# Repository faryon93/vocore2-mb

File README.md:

# VoCore2 Motherboard

* 1x Ethernet Breakout
* 3x Mini-PCIe Slot (USB Connection via USB 2.0 Hub)
* MicroSD Card
* FTDI console UART
* Passive PoE or Phoenix-style connector for power
* Buzzer
* SPI Flash Breakout Header

## Board

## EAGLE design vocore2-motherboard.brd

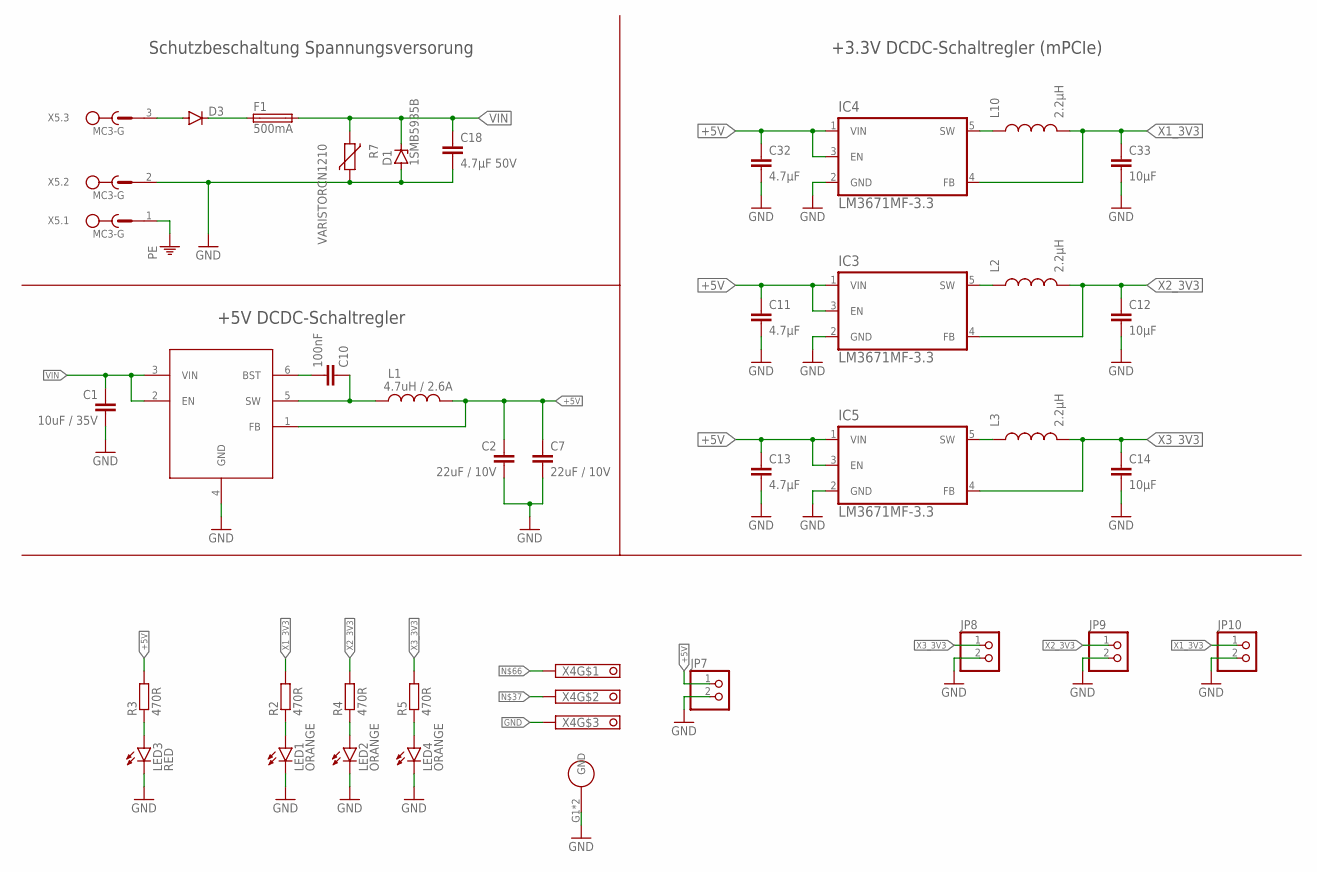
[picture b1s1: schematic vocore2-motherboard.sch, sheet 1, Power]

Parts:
C1: 10uF / 35V; C0805; DIGIKEY 490-13248-1-ND
C2, C7: 22uF / 10V; C0805; DIGIKEY 490-10511-1-ND
C10: 100nF; C0805
C11, C13, C32: 4.7µF; C0603; DIGIKEY 1276-2087-1-ND
C12, C14, C33: 10µF; C0603
C18: 4.7µF 50V; C1206; DIGIKEY 587-2994-1-ND
D1: 1SMB5935B; SMB; FARNELL 1431177
D3: DIODE-SMB; SMB; FARNELL 1858651
F1: 500mA; 1812; LCSC C17313
IC1: AP63205; SOT23-6
IC3, IC4, IC5: LM3671MF-3.3; SOT95P284X122-5N; DIGIKEY LM3671MF-3.3/NOPBCT-ND
JP7: PINHD-1X2_2.54; 1X02
JP8, JP9, JP10: PINHD-1X2; 1X02
L1: 4.7uH / 2.6A; 4.90X4.90; DIGIKEY 587-3605-2-ND
L2, L3, L10: 2.2µH; SO3314; DIGIKEY 445-8725-1-ND
LED1, LED2, LED4: ORANGE; CHIP-LED0805; DIGIKEY 160-1445-1-ND
LED3: RED; CHIP-LED0805; DIGIKEY 160-1447-1-ND
R2, R3, R4, R5: 470R; R0603
R7: VARISTORCN1210; CT/CN1210; FARNELL 1636457
X4: BM03B-SRSS-TB
X5: MC3-G; DIGIKEY ‎277-1207-ND‎;‎277-13872-ND‎

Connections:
+5V: C2.1, C7.1, C11.1, C13.1, C32.1, IC1.1 (FB), IC3.1 (VIN), IC3.3 (EN), IC4.1 (VIN), IC4.3 (EN), IC5.1 (VIN), IC5.3 (EN), JP7.1, L1.P$2 (2), R3.2; also elsewhere on the board
+24V: D3.C, F1.1; also elsewhere on the board
GND: C1.2, C2.2, C7.2, C11.2, C12.2, C13.2, C14.2, C18.2, C32.2, C33.2, D1.A, IC1.4 (GND), IC3.2 (GND), IC4.2 (GND), IC5.2 (GND), JP7.2, JP8.2, JP9.2, JP10.2, LED1.C, LED2.C, LED3.C, LED4.C, R7.1, X4.3 (K), X4.G1 (GND), X4.G2 (GND), X5.2; also elsewhere on the board
unnamed: C10.1, IC1.5 (SW), L1.P$1 (1)
unnamed: IC3.5 (SW), L2.1
unnamed: IC5.5 (SW), L3.1
unnamed: LED3.A, R3.1
unnamed: LED1.A, R2.1
unnamed: LED2.A, R4.1
unnamed: LED4.A, R5.1
unnamed 43: X4.2 (K); also elsewhere on the board
unnamed: IC4.5 (SW), L10.1
unnamed: D3.A, X5.3
unnamed: C10.2, IC1.6 (BST)
unnamed 65: X4.1 (K); also elsewhere on the board
PE: X5.1
VIN: C1.1, C18.1, D1.C, F1.2, IC1.2 (EN), IC1.3 (VIN), R7.2
X1_3V3: C33.1, IC4.4 (FB), JP10.1, L10.2, R2.2; also elsewhere on the board
X2_3V3: C12.1, IC3.4 (FB), JP9.1, L2.2, R4.2; also elsewhere on the board
X3_3V3: C14.1, IC5.4 (FB), JP8.1, L3.2, R5.2; also elsewhere on the board

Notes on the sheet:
Schutzbeschaltung Spannungsversorung
+5V DCDC-Schaltregler
+3.3V DCDC-Schaltregler (mPCIe)

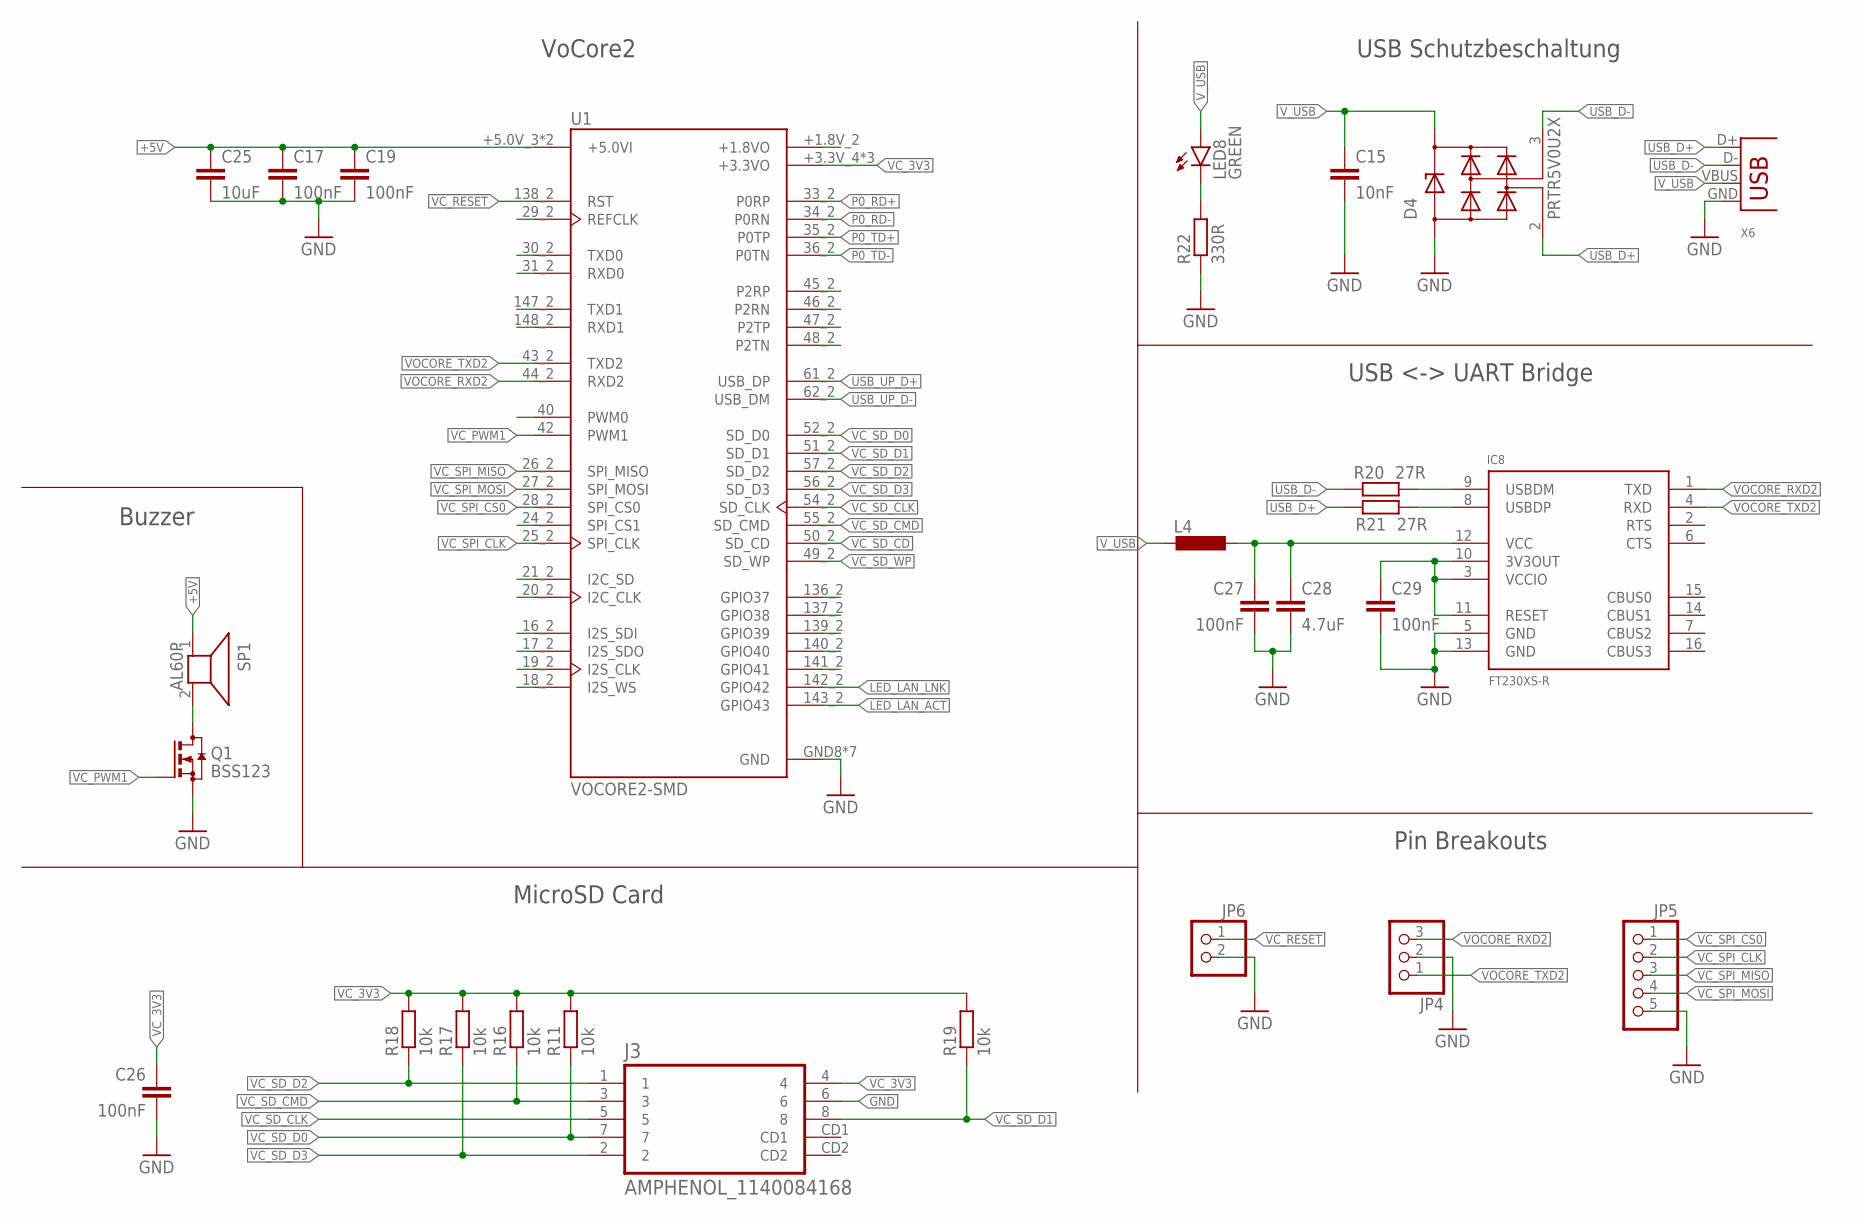
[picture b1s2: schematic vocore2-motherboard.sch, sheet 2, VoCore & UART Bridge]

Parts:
C15: 10nF; C0603
C17, C19, C26, C27, C29: 100nF; C0603
C25: 10uF; C0603
C28: 4.7uF; C0603
D4: PRTR5V0U2X; SOT143; DIGIKEY 1727-3884-1-ND
IC8: FT230XS-R; SSOP16-0.635-5X4MM
J3: AMPHENOL_1140084168
JP4: PINHD-1X3; 1X03
JP5: PINHD-1X5; 1X05
JP6: PINHD-1X2_2.54; 1X02
L4: L-EUL0805; L0805; DIGIKEY 490-1054-1-ND
LED8: GREEN; CHIP-LED0805; DIGIKEY 160-1446-1-ND
Q1: BSS123; SOT23; DIGIKEY BSS123LT1GOSCT-ND‎
R11, R16, R17, R18, R19: 10k; R0603
R20, R21: 27R; R0603
R22: 330R; R0603
SP1: AL60P; LCSC C252917
U1: VOCORE2-SMD; VOCORE2_SMD
X6: USB-MB-S

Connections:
!VC_RESET: JP6.1, U1.138_2 (RST)
+5V: C17.1, C19.1, C25.1, SP1.1, U1.+5.0V_3 (+5.0VI), U1.+5.0V_4 (+5.0VI); also elsewhere on the board
FT230_VCCIO: C29.1, IC8.3 (VCCIO), IC8.10 (3V3OUT), IC8.11 (RESET)
GND: C15.2, C17.2, C19.2, C25.2, C26.2, C27.2, C28.2, C29.2, D4.1 (GND), IC8.5 (GND), IC8.13 (GND), J3.6, JP4.2, JP5.5, JP6.2, Q1.2 (S), R22.1, U1.GND8 (GND), U1.GND9 (GND), U1.GND10 (GND), U1.GND11 (GND), U1.GND12 (GND), U1.GND13 (GND), U1.GND14 (GND), X6.GND; also elsewhere on the board
LED_LAN_ACT: U1.143_2 (GPIO43); also elsewhere on the board
LED_LAN_LNK: U1.142_2 (GPIO42); also elsewhere on the board
unnamed: Q1.3 (D), SP1.2
unnamed: C27.1, C28.1, IC8.12 (VCC), L4.1
unnamed: IC8.9 (USBDM), R20.2
unnamed: IC8.8 (USBDP), R21.1
unnamed: LED8.C, R22.2
P0_RD+: U1.33_2 (P0RP); also elsewhere on the board
P0_RD-: U1.34_2 (P0RN); also elsewhere on the board
P0_TD+: U1.35_2 (P0TP); also elsewhere on the board
P0_TD-: U1.36_2 (P0TN); also elsewhere on the board
USB_D+: D4.2 (IO1), R21.2, X6.D+
USB_D-: D4.3 (IO2), R20.1, X6.D-
USB_UP_D+: U1.61_2 (USB_DP); also elsewhere on the board
USB_UP_D-: U1.62_2 (USB_DM); also elsewhere on the board
VC_3V3: C26.1, J3.4, R11.2, R16.2, R17.2, R18.2, R19.2, U1.+3.3V_4 (+3.3VO), U1.+3.3V_5 (+3.3VO), U1.+3.3V_6 (+3.3VO); also elsewhere on the board
VC_PWM1: Q1.1 (G), U1.42 (PWM1)
VC_SD_CD: U1.50_2 (SD_CD)
VC_SD_CLK: J3.5, U1.54_2 (SD_CLK)
VC_SD_CMD: J3.3, R16.1, U1.55_2 (SD_CMD)
VC_SD_D0: J3.7, R11.1, U1.52_2 (SD_D0)
VC_SD_D1: J3.8, R19.1, U1.51_2 (SD_D1)
VC_SD_D2: J3.1, R18.1, U1.57_2 (SD_D2)
VC_SD_D3: J3.2, R17.1, U1.56_2 (SD_D3)
VC_SD_WP: U1.49_2 (SD_WP)
VC_SPI_CLK: JP5.2, U1.25_2 (SPI_CLK)
VC_SPI_CS0: JP5.1, U1.28_2 (SPI_CS0)
VC_SPI_MISO: JP5.3, U1.26_2 (SPI_MISO)
VC_SPI_MOSI: JP5.4, U1.27_2 (SPI_MOSI)
VOCORE_RXD2: IC8.1 (TXD), JP4.3, U1.44_2 (RXD2)
VOCORE_TXD2: IC8.4 (RXD), JP4.1, U1.43_2 (TXD2)
V_USB: C15.1, D4.4 (VCC), L4.2, LED8.A, X6.VBUS

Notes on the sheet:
USB Schutzbeschaltung
Pin Breakouts
USB <-> UART Bridge
VoCore2
MicroSD Card
Buzzer

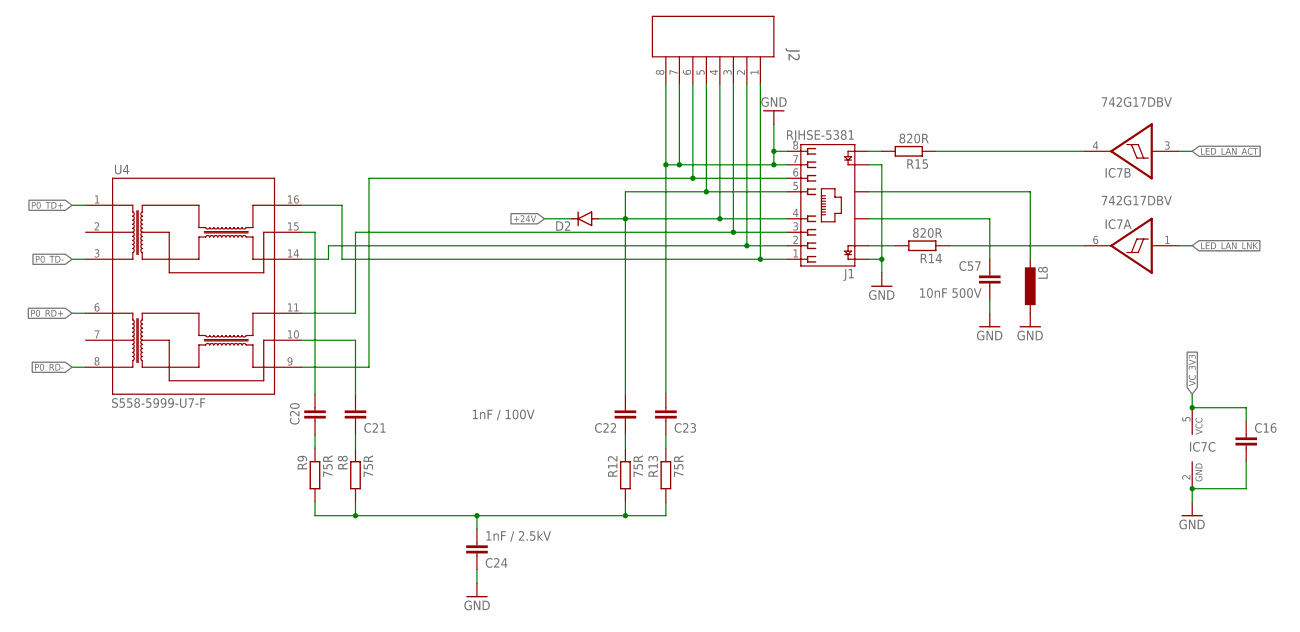
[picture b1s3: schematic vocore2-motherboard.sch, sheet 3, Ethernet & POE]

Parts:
C16: 100nF; C0603; DIGIKEY 490-4780-1-ND
C20, C21, C22, C23: 1nF / 100V; C0603; DIGIKEY 490-4780-1-ND
C24: 1nF / 2.5kV; C1808; DIGIKEY 399-7246-1-ND
C57: 10nF 500V; C0805; DIGIKEY 709-1021-1-ND
D2: DIODE-SMB; SMB; FARNELL 1858651
IC7: 742G17DBV; DBV_R-PDSO-G6; DIGIKEY 296-13010-1-ND
J1: RJHSE-5381; AMPHENOL_RJHSE-5381
J2: TE_1775470-8; CONN8_1775470-8; DIGIKEY A100058CT-ND
L8: L-EUL0805; L0805; DIGIKEY 490-1054-1-ND
R8, R9, R12, R13: 75R; R0603; DIGIKEY RNCP0603FTD75R0CT-ND‎
R14, R15: 820R; R0603; DIGIKEY A129687CT-ND
U4: S558-5999-U7-F

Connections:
+24V: D2.C; also elsewhere on the board
GND: C16.2, C23.2, C24.1, C57.2, IC7.2 (GND), J1.7, J1.8, J1.9, J1.11, J2.7, J2.8, L8.1; also elsewhere on the board
LED_LAN_ACT: IC7.3 (I); also elsewhere on the board
LED_LAN_LNK: IC7.1 (I); also elsewhere on the board
unnamed: C20.2, U4.15 (TX_CT)
unnamed: C21.2, U4.10 (RX_CT)
unnamed: C21.1, R8.1
unnamed: C20.1, R9.1
unnamed: C22.1, R12.1
unnamed: C23.1, R13.1
unnamed: C24.2, R8.2, R9.2, R12.2, R13.2
unnamed 43: IC7.4 (O), R15.1; also elsewhere on the board
unnamed: J1.12, R15.2
unnamed: J1.10, R14.2
unnamed: J1.S2, L8.2
unnamed: C57.1, J1.S1
unnamed 65: IC7.6 (O), R14.1; also elsewhere on the board
P0_RD+: U4.6 (RD+); also elsewhere on the board
P0_RD-: U4.8 (RD-); also elsewhere on the board
P0_TD+: U4.1 (TD+); also elsewhere on the board
P0_TD-: U4.3 (TD-); also elsewhere on the board
POE_V+: C22.2, D2.A, J1.4, J1.5, J2.4, J2.5
RX+: J1.3, J2.3, U4.11 (RX+)
RX-: J1.6, J2.6, U4.9 (RX-)
TX+: J1.1, J2.1, U4.16 (TX+)
TX-: J1.2, J2.2, U4.14 (TX-)
VC_3V3: C16.1, IC7.5 (VCC); also elsewhere on the board

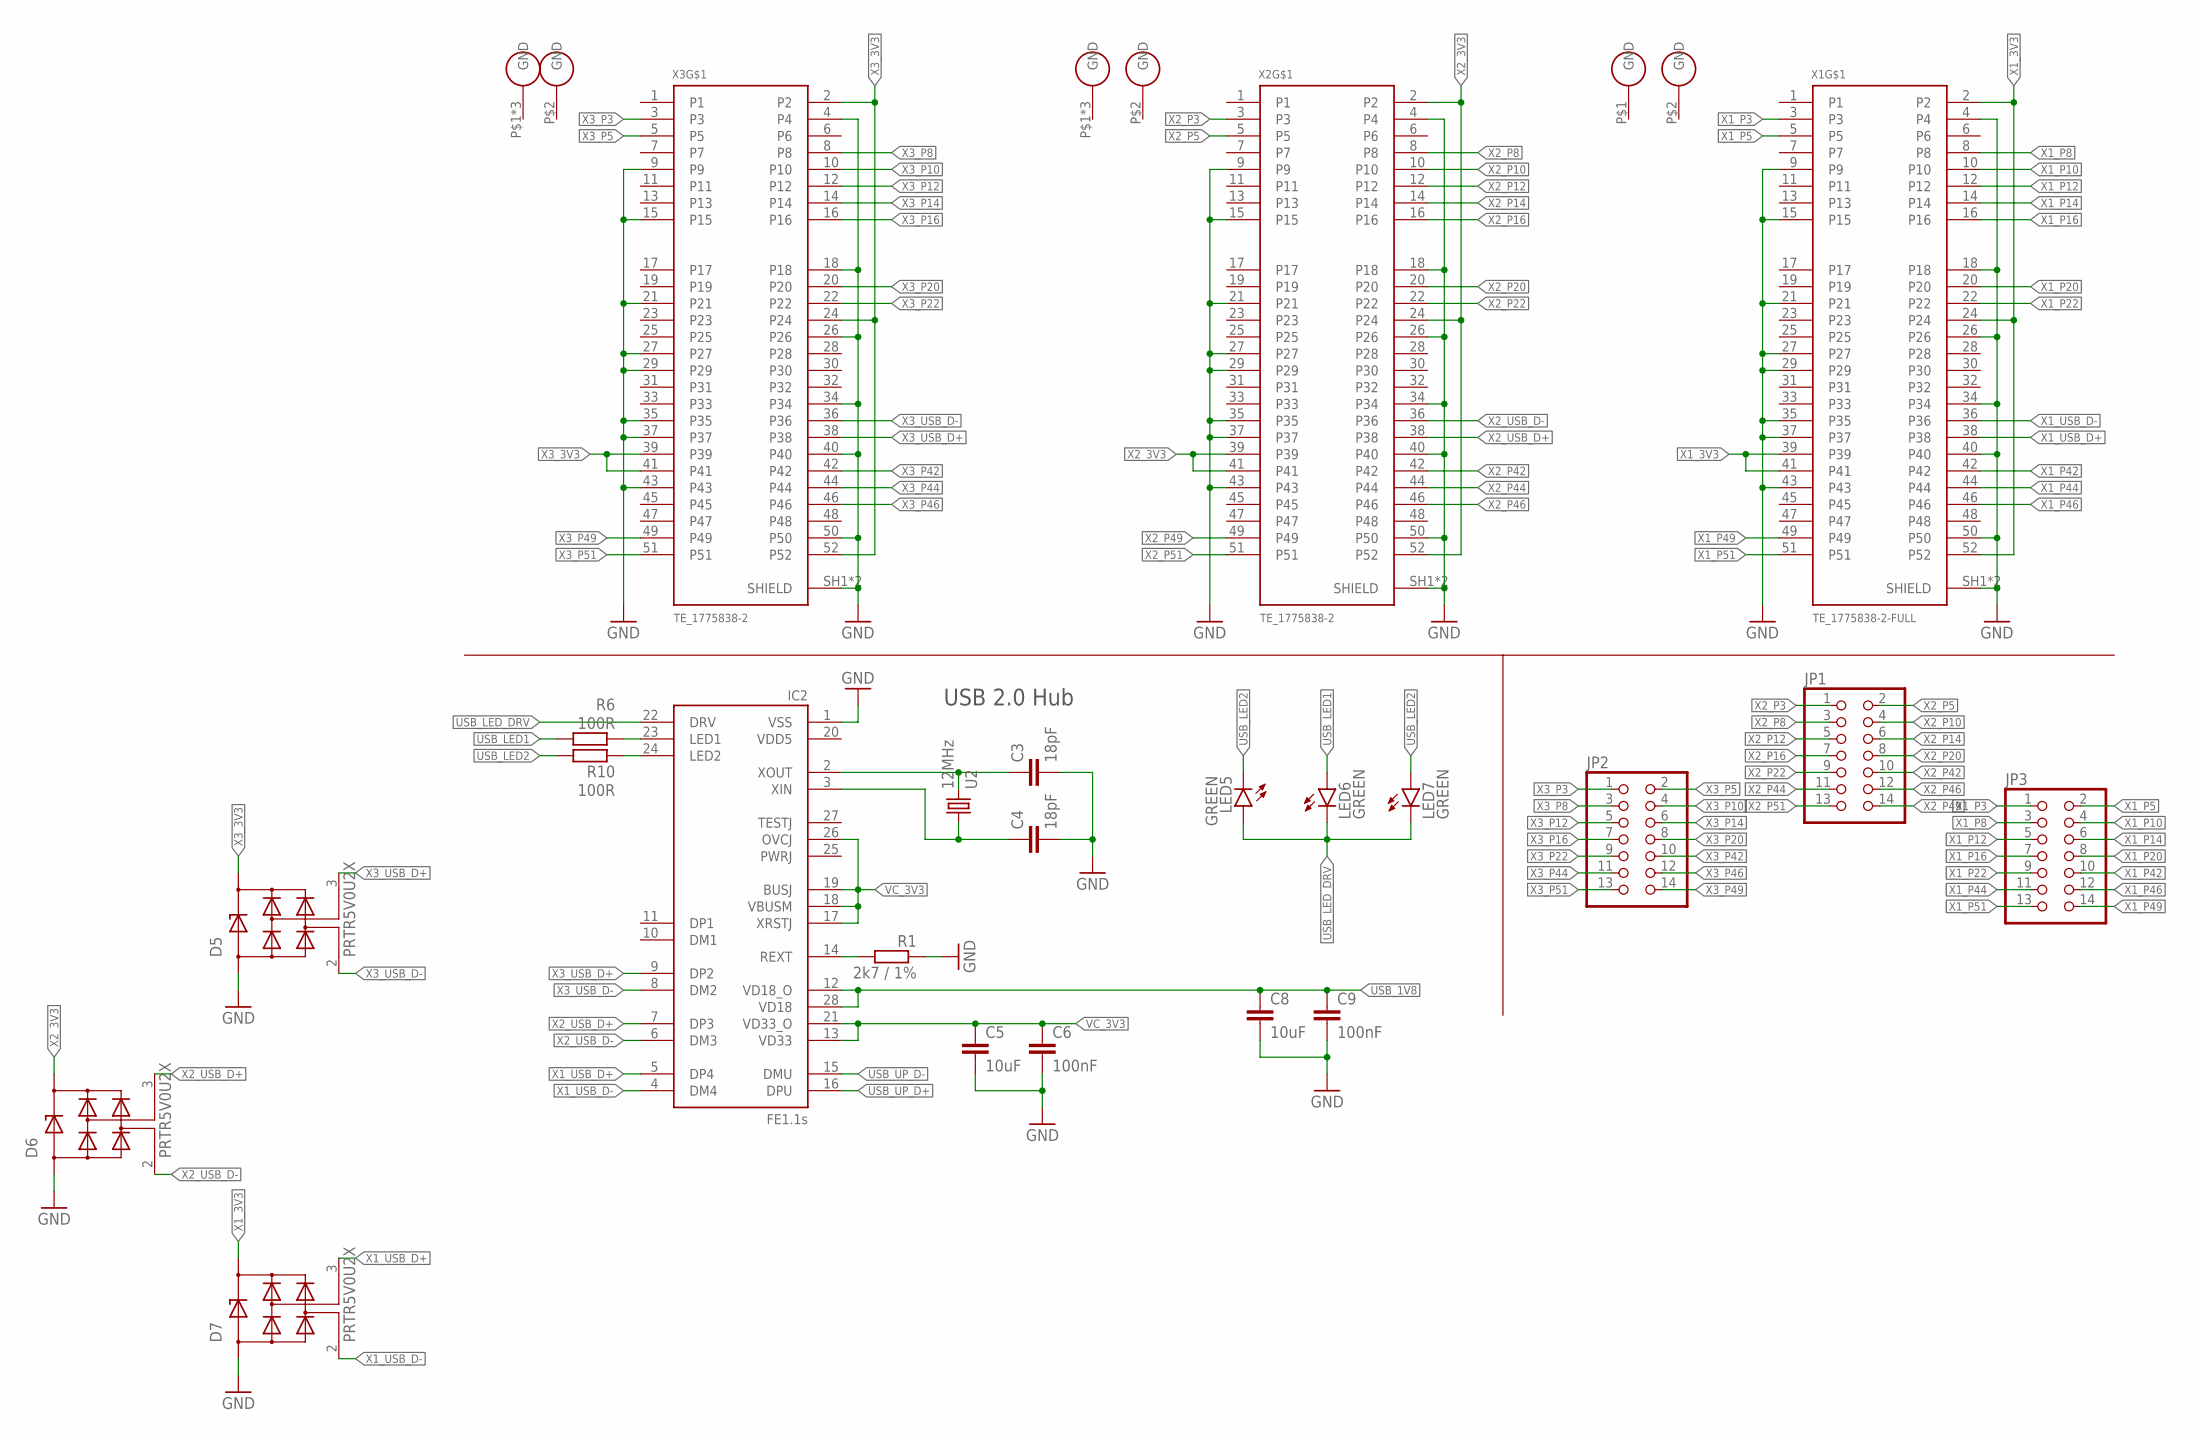
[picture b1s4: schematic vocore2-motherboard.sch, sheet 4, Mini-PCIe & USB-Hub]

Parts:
C3, C4: 18pF; C0603
C5, C8: 10uF; C0603
C6, C9: 100nF; C0603
D5, D6, D7: PRTR5V0U2X; SOT143; DIGIKEY 1727-3884-1-ND
IC2: FE1.1S; FE1.1S_SSOP-28
JP1, JP2, JP3: PINHD-2X7; 2X07
LED5, LED6, LED7: GREEN; CHIP-LED0805; DIGIKEY 160-1446-1-ND
R1: 2k7 / 1%; R0603; DIGIKEY RR08P2.7KDCT-ND
R6, R10: 100R; R0603
U2: 12MHz; 7A; FARNELL 1841940
X1: TE_1775838-2-FULL
X2, X3: TE_1775838-2

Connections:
GND: C3.2, C4.2, C5.2, C6.2, C8.2, C9.2, D5.1 (GND), D6.1 (GND), D7.1 (GND), IC2.1 (VSS), R1.1, X1.4, X1.9, X1.15, X1.18, X1.21, X1.26, X1.27, X1.29, X1.34, X1.35, X1.37, X1.40, X1.43, X1.50, X1.P$1 (GND), X1.P$2 (GND), X1.SH1 (SHIELD), X1.SH2 (SHIELD), X2.4, X2.9, X2.15, X2.18, X2.21, X2.26, X2.27, X2.29, X2.34, X2.35, X2.37, X2.40, X2.43, X2.50, X2.P$1 (GND), X2.P$2 (GND), X2.P$3 (GND), X2.P$4 (GND), X2.SH1 (SHIELD), X2.SH2 (SHIELD), X3.4, X3.9, X3.15, X3.18, X3.21, X3.26, X3.27, X3.29, X3.34, X3.35, X3.37, X3.40, X3.43, X3.50, X3.P$1 (GND), X3.P$2 (GND), X3.P$3 (GND), X3.P$4 (GND), X3.SH1 (SHIELD), X3.SH2 (SHIELD); also elsewhere on the board
unnamed: C3.1, IC2.2 (XOUT), U2.2
unnamed: C4.1, IC2.3 (XIN), U2.1
unnamed: IC2.14 (REXT), R1.2
unnamed: IC2.23 (LED1), R6.1
unnamed: IC2.24 (LED2), R10.1
USB_1V8: C8.1, C9.1, IC2.12 (VD18_O), IC2.28 (VD18)
USB_LED1: LED6.A, R6.2
USB_LED2: LED5.C, LED7.A, R10.2
USB_LED_DRV: IC2.22 (DRV), LED5.A, LED6.C, LED7.C
USB_UP_D+: IC2.16 (DPU); also elsewhere on the board
USB_UP_D-: IC2.15 (DMU); also elsewhere on the board
VC_3V3: C5.1, C6.1, IC2.13 (VD33), IC2.17 (XRSTJ), IC2.18 (VBUSM), IC2.19 (BUSJ), IC2.21 (VD33_O), IC2.26 (OVCJ); also elsewhere on the board
X1_3V3: D7.4 (VCC), X1.2, X1.24, X1.39, X1.41, X1.52; also elsewhere on the board
X1_P3: JP3.1, X1.3
X1_P5: JP3.2, X1.5
X1_P8: JP3.3, X1.8
X1_P10: JP3.4, X1.10
X1_P12: JP3.5, X1.12
X1_P14: JP3.6, X1.14
X1_P16: JP3.7, X1.16
X1_P20: JP3.8, X1.20
X1_P22: JP3.9, X1.22
X1_P42: JP3.10, X1.42
X1_P44: JP3.11, X1.44
X1_P46: JP3.12, X1.46
X1_P49: JP3.14, X1.49
X1_P51: JP3.13, X1.51
X1_USB_D+: D7.3 (IO2), IC2.5 (DP4), X1.38
X1_USB_D-: D7.2 (IO1), IC2.4 (DM4), X1.36
X2_3V3: D6.4 (VCC), X2.2, X2.24, X2.39, X2.41, X2.52; also elsewhere on the board
X2_P3: JP1.1, X2.3
X2_P5: JP1.2, X2.5
X2_P8: JP1.3, X2.8
X2_P10: JP1.4, X2.10
X2_P12: JP1.5, X2.12
X2_P14: JP1.6, X2.14
X2_P16: JP1.7, X2.16
X2_P20: JP1.8, X2.20
X2_P22: JP1.9, X2.22
X2_P42: JP1.10, X2.42
X2_P44: JP1.11, X2.44
X2_P46: JP1.12, X2.46
X2_P49: JP1.14, X2.49
X2_P51: JP1.13, X2.51
X2_USB_D+: D6.3 (IO2), IC2.7 (DP3), X2.38
X2_USB_D-: D6.2 (IO1), IC2.6 (DM3), X2.36
X3_3V3: D5.4 (VCC), X3.2, X3.24, X3.39, X3.41, X3.52; also elsewhere on the board
X3_P3: JP2.1, X3.3
X3_P5: JP2.2, X3.5
X3_P8: JP2.3, X3.8
X3_P10: JP2.4, X3.10
X3_P12: JP2.5, X3.12
X3_P14: JP2.6, X3.14
X3_P16: JP2.7, X3.16
X3_P20: JP2.8, X3.20
X3_P22: JP2.9, X3.22
X3_P42: JP2.10, X3.42
X3_P44: JP2.11, X3.44
X3_P46: JP2.12, X3.46
X3_P49: JP2.14, X3.49
X3_P51: JP2.13, X3.51
X3_USB_D+: D5.3 (IO2), IC2.9 (DP2), X3.38
X3_USB_D-: D5.2 (IO1), IC2.8 (DM2), X3.36

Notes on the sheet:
USB 2.0 Hub

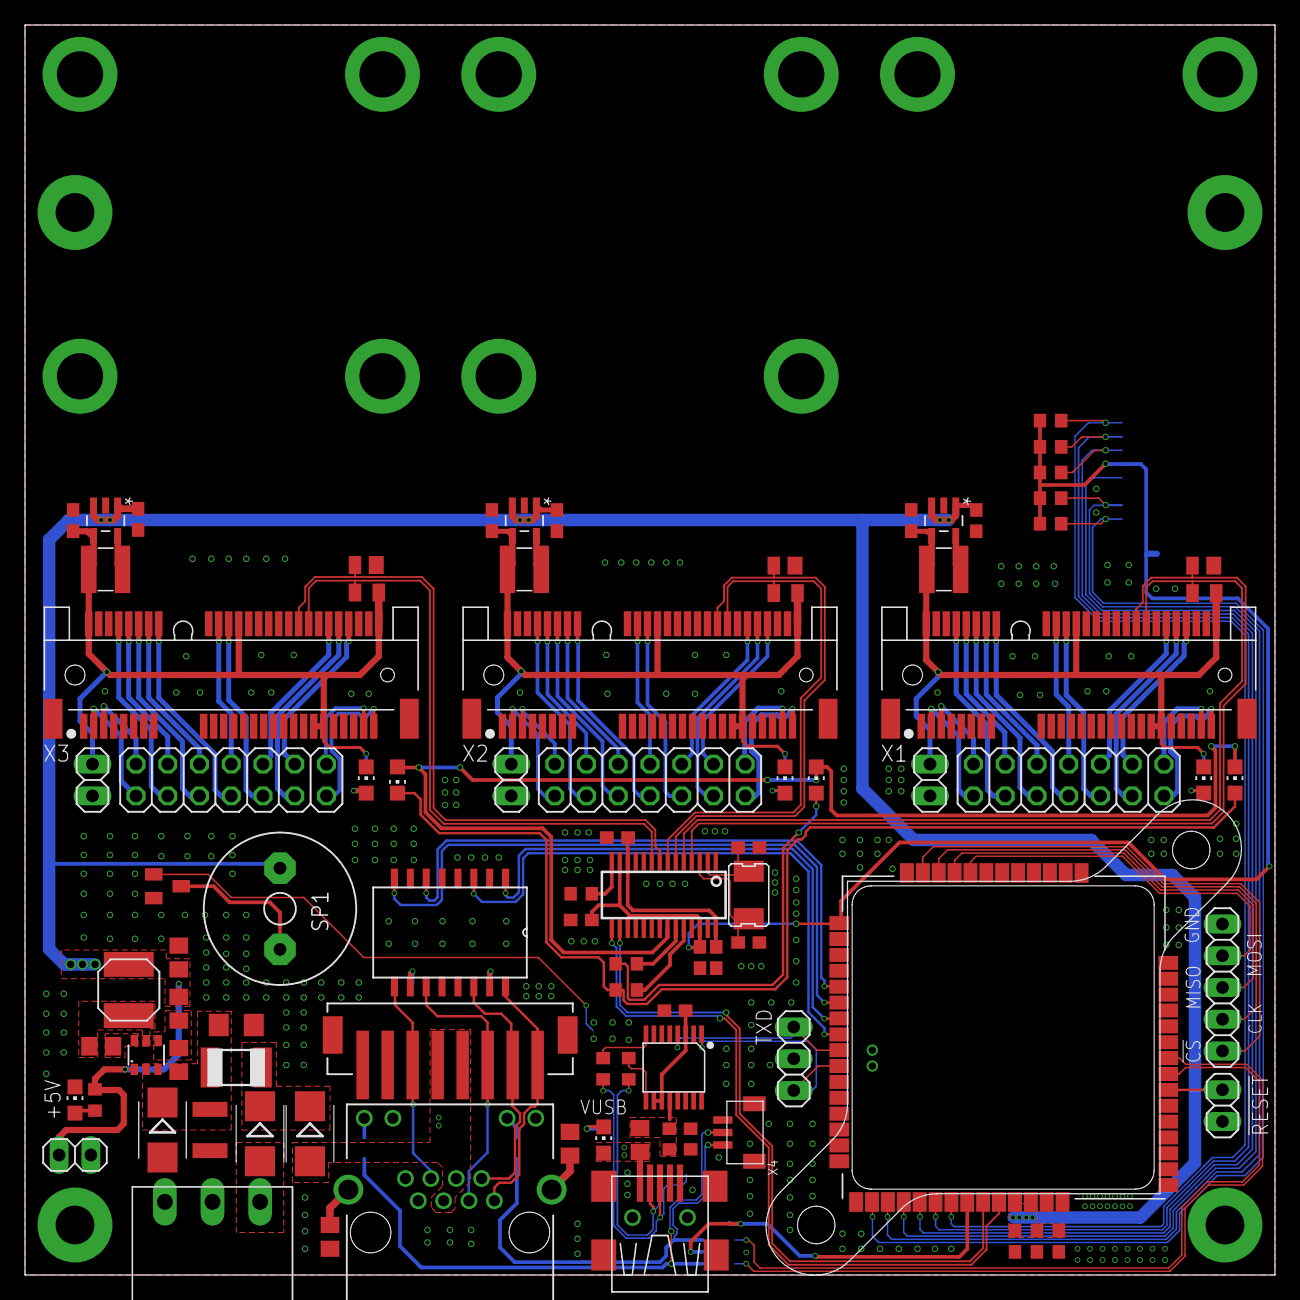
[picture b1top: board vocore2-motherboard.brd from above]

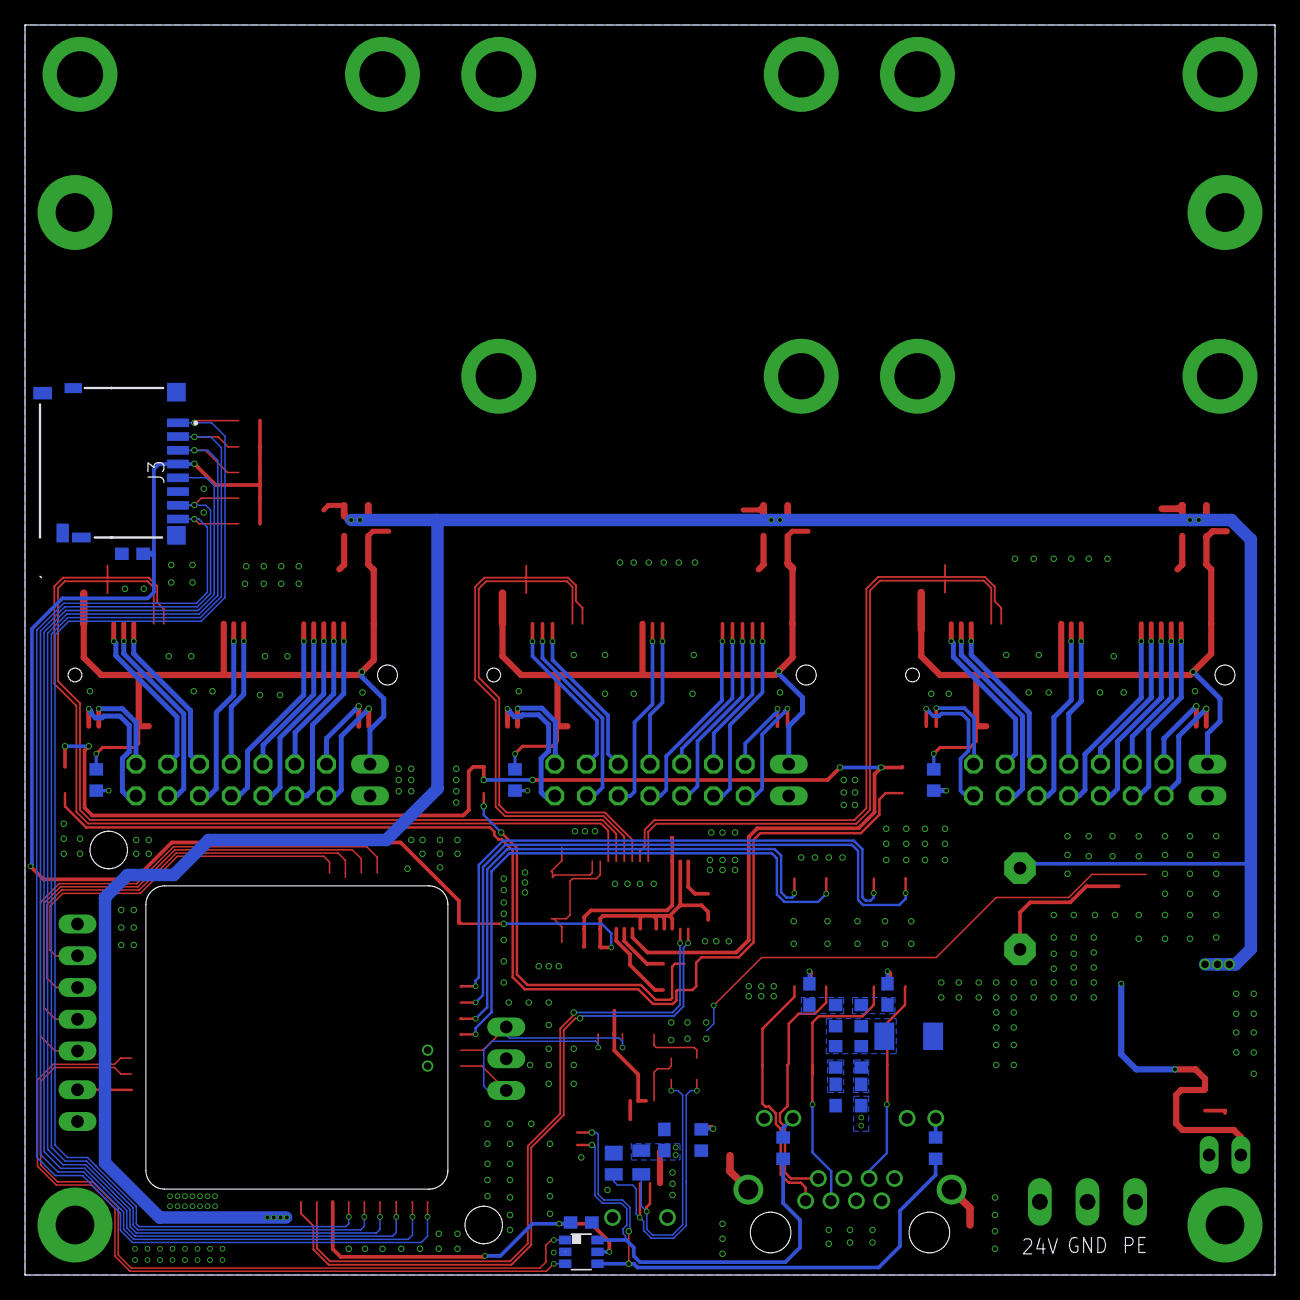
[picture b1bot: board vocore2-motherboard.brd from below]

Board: 2 copper layers, 100.0 x 100.0 mm, 108 parts (21 on the bottom side), 124 nets.

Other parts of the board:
U$1: ATS-P1-138-C2-R0

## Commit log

2019-11-04 fix: moved LAN_LED_ACT to gpio43
    gpio43 can be configured to represent the LNK/ACT state of the Ethernt
    PHYs Port 0.
2019-11-04 fix: typo in partname LM3761MF -> LM3671MF
2019-11-04 feat: added digikey part numbers
2019-11-04 fix: proper colors for leds
    PWR = red
    MPCIE_PWR = orange
    MPCIE_USB = green
2019-11-04 fix: corrected led restistor values
2019-11-04 fix: some more digikey part numbers
2019-11-04 refactor: new symbol for ethernet transformer U4
2019-11-04 fix: switched SD_D0 and SD_D1
2019-11-12 fix(p0led): use inverting-buffer to drive lan leds
2019-11-12 feat(sch): cleanup page 3 vocore & uart bridge
2019-11-12 feat: use FT230X instead of FT232R
2019-11-12 feat(pcb): mounting hole for vocore
2019-11-12 fix(brd): proper heatsink dimensions
2019-11-12 feat: LED für V_USB
2019-11-12 feat(brd): threaded inserts for PCIe half-sized card (X3 and X2 only)
2019-11-12 fix: changed led resistor values
2019-11-13 fix(pcb): reconnected buzzer
2019-11-13 feat: 3V3 + GND pinheader for each minipcie-slot
2019-11-13 fix: use non-inverting buffers to drive lan leds
    The rt3050 ethernet switch, integrated on the SoC, has the ability to
    configure led polarity. Therefore it is not necessary to fix the
    active-low problem in hardware.
2019-11-13 feat(pcb): skylabs SKW92A outline
2019-11-13 feat(pcb): Beschriftung Phoenix Stromstecker
2019-11-14 feat: TVS diodes on MiniPCIe slots
2019-11-16 feat: network led breakout
2019-12-21 feat(pcb): removed through-hole mounts for vocore2
2019-12-21 fix: tPlace outline for all ICs
2019-12-21 feat(readme): added basic readme with pcb screenshot
2019-12-21 fix(readme): rotated pcb screenshot
2019-12-21 fix(readme): typos
2022-08-10 Add .gitattributes
